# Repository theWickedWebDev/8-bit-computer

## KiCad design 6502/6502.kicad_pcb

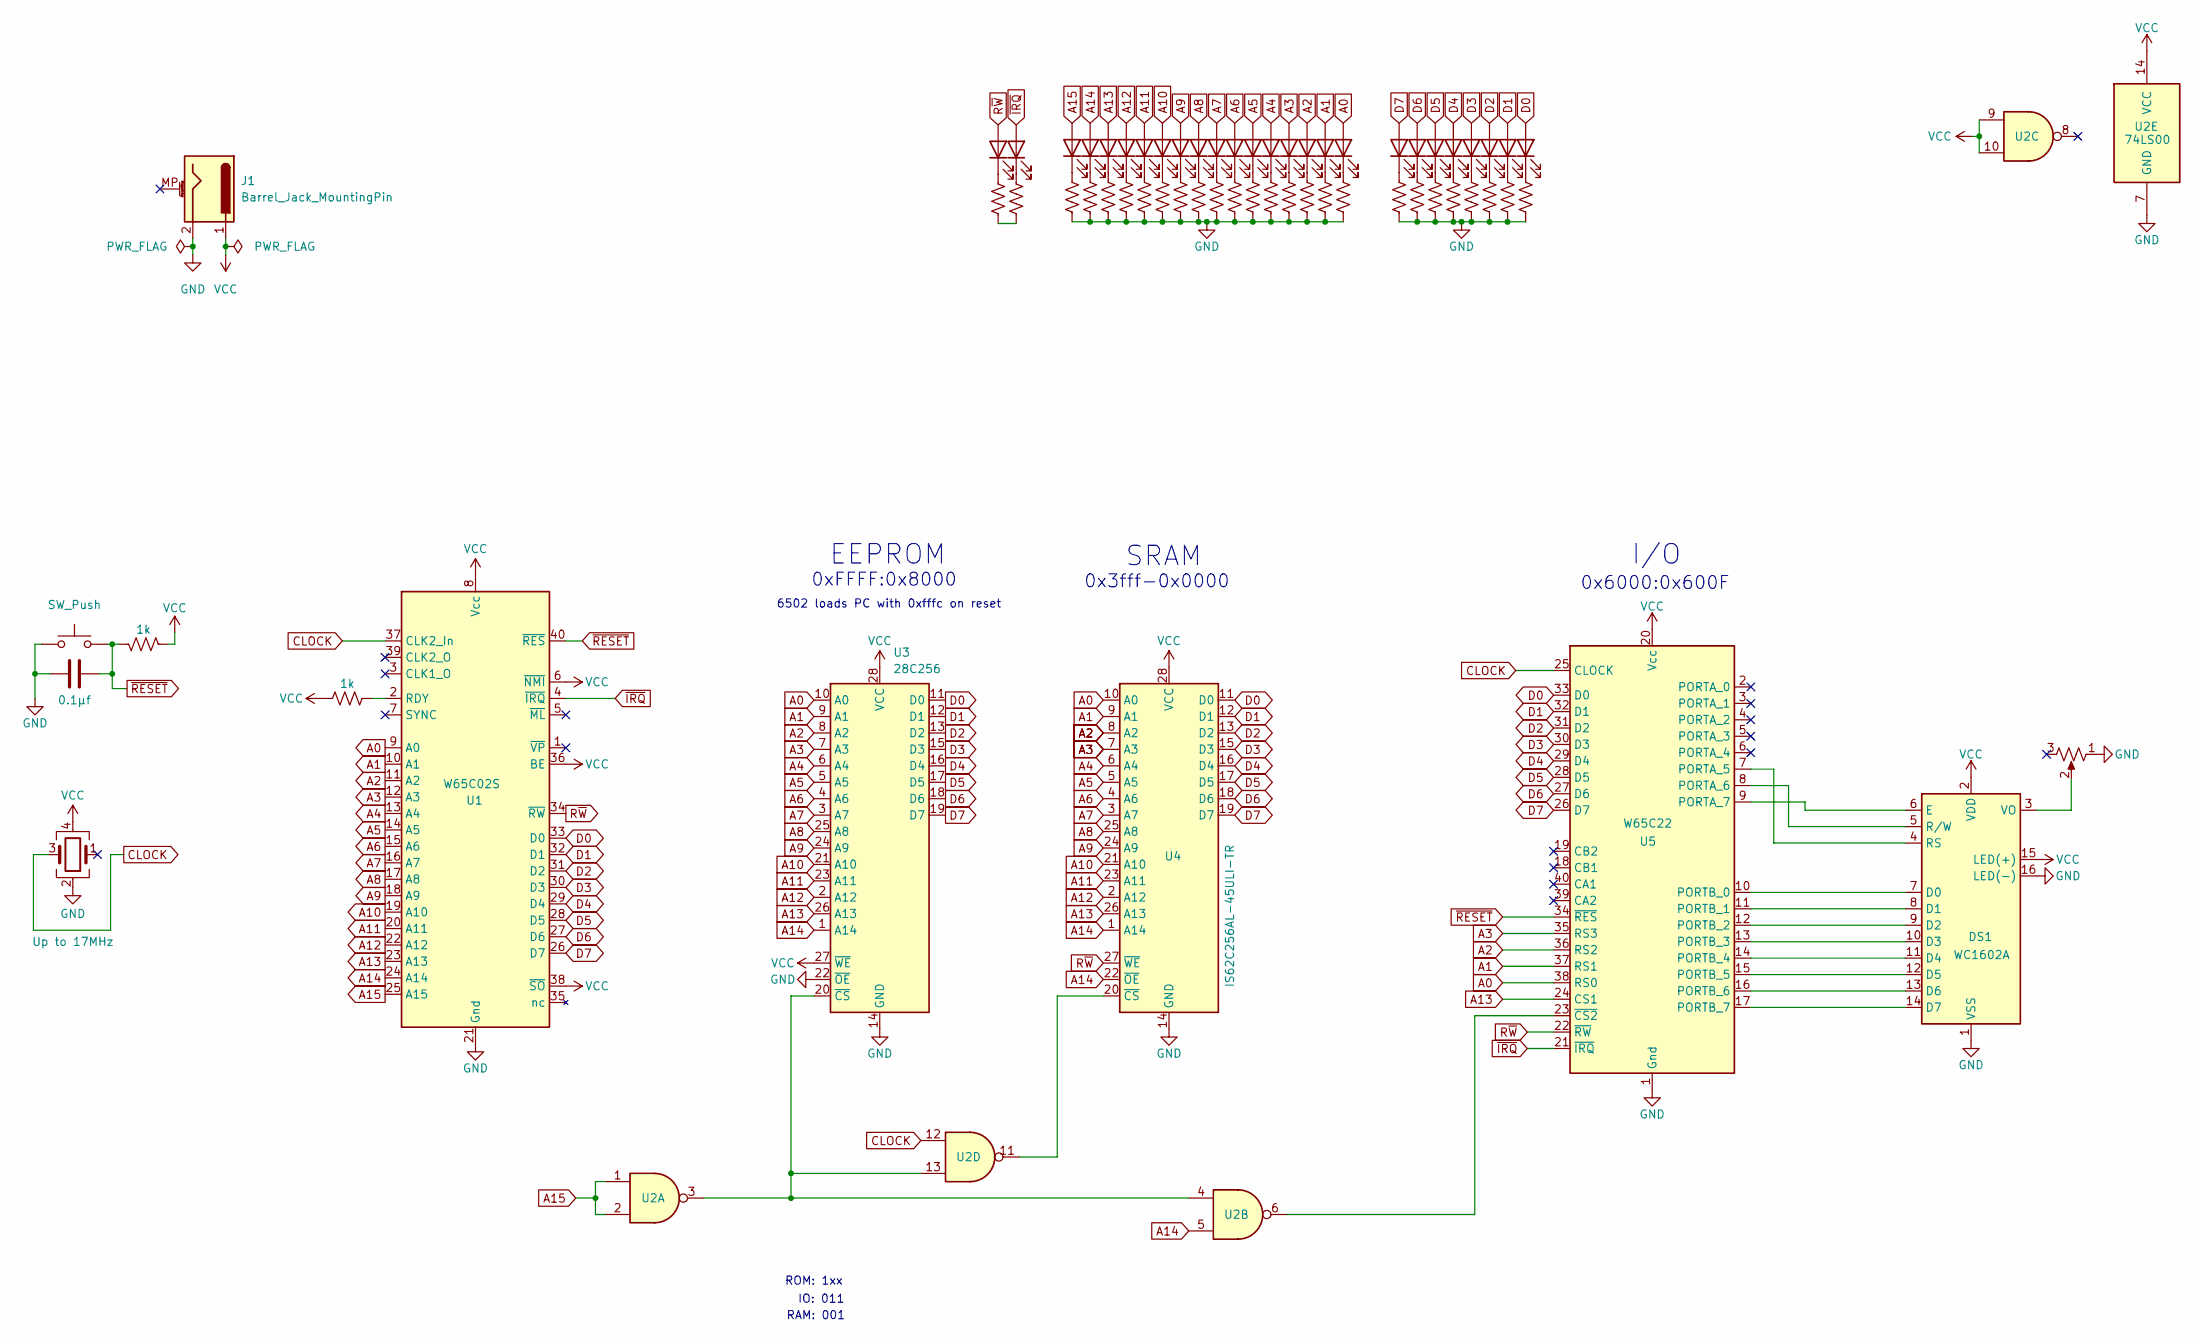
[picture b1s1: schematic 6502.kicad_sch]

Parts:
C1: C; C_0805_2012Metric
D1, D2, D3, D4, D5, D6, D7, D8, D9, D10, D11, D12, D13, D14, D15, D16, D17, D18, D19, D20, D21, D22, D23, D24, D25, D26: LED; LED_0805_2012Metric
DS1: WC1602A
J1: Barrel_Jack_MountingPin; BarrelJack_Horizontal
R1, R2, R3, R4, R5, R6, R7, R8, R9, R10, R11, R12, R13, R14, R15, R16, R17, R18, R19, R20, R21, R22, R23, R24, R25, R26, R27, R28: R_US; R_0805_2012Metric
RV1: R_Potentiometer_US; Potentiometer_Bourns_3224J_Horizontal
SW1: SW_Push; SW_PUSH_6mm
U1: W65C02S; PQFP-44_10x10mm_P0.8mm
U2: 74LS00; TSSOP-14_4.4x5mm_P0.65mm
U3: 28C256; Microchip-32J-10_2001-B-IPC_A
U4: IS62C256AL-45ULI-TR; SOIC-28W_7.5x17.9mm_P1.27mm
U5: W65C22; PQFP-44_10x10mm_P0.8mm
Y1: Crystal_GND24; Crystal_SMD_Abracon_ABM3C-4Pin_5.0x3.2mm

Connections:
A0: D18.2 (A), U1.9 (A0), U3.10 (A0), U4.10 (A0), U5.38 (RS0)
A1: D17.2 (A), U1.10 (A1), U3.9 (A1), U4.9 (A1), U5.37 (RS1)
A2: D16.2 (A), U1.11 (A2), U3.8 (A2), U4.8 (A2), U5.36 (RS2)
A3: D15.2 (A), U1.12 (A3), U3.7 (A3), U4.7 (A3), U5.35 (RS3)
A4: D14.2 (A), U1.13 (A4), U3.6 (A4), U4.6 (A4)
A5: D13.2 (A), U1.14 (A5), U3.5 (A5), U4.5 (A5)
A6: D12.2 (A), U1.15 (A6), U3.4 (A6), U4.4 (A6)
A7: D11.2 (A), U1.16 (A7), U3.3 (A7), U4.3 (A7)
A8: D10.2 (A), U1.17 (A8), U3.25 (A8), U4.25 (A8)
A9: D9.2 (A), U1.18 (A9), U3.24 (A9), U4.24 (A9)
A10: D8.2 (A), U1.19 (A10), U3.21 (A10), U4.21 (A10)
A11: D7.2 (A), U1.20 (A11), U3.23 (A11), U4.23 (A11)
A12: D6.2 (A), U1.22 (A12), U3.2 (A12), U4.2 (A12)
A13: D5.2 (A), U1.23 (A13), U3.26 (A13), U4.26 (A13), U5.24 (CS1)
A14: D4.2 (A), U1.24 (A14), U2.5, U3.1 (A14), U4.1 (A14), U4.22 (~OE)
A15: D3.2 (A), U1.25 (A15), U2.1, U2.2
CLOCK: U1.37 (CLK2_In), U2.12, U5.25 (CLOCK), Y1.3
D0: D26.2 (A), U1.33 (D0), U3.11 (D0), U4.11 (D0), U5.33 (D0)
D1: D25.2 (A), U1.32 (D1), U3.12 (D1), U4.12 (D1), U5.32 (D1)
D2: D24.2 (A), U1.31 (D2), U3.13 (D2), U4.13 (D2), U5.31 (D2)
D3: D23.2 (A), U1.30 (D3), U3.15 (D3), U4.15 (D3), U5.30 (D3)
D4: D22.2 (A), U1.29 (D4), U3.16 (D4), U4.16 (D4), U5.29 (D4)
D5: D21.2 (A), U1.28 (D5), U3.17 (D5), U4.17 (D5), U5.28 (D5)
D6: D20.2 (A), U1.27 (D6), U3.18 (D6), U4.18 (D6), U5.27 (D6)
D7: D19.2 (A), U1.26 (D7), U3.19 (D7), U4.19 (D7), U5.26 (D7)
GND: C1.2, DS1.1 (VSS), DS1.16 (LED(-)), J1.2, R5.1, R6.1, R7.1, R8.1, R9.1, R10.1, R11.1, R12.1, R13.1, R14.1, R15.1, R16.1, R17.1, R18.1, R19.1, R20.1, R21.1, R22.1, R23.1, R24.1, R25.1, R26.1, R27.1, R28.1, RV1.1, SW1.2, U1.21 (Gnd), U2.7 (GND), U3.14 (GND), U3.22 (~OE), U4.14 (GND), U5.1 (Gnd), Y1.2
unnamed: D1.1 (K), R3.2
unnamed: D2.1 (K), R4.2
unnamed: D3.1 (K), R5.2
unnamed: D4.1 (K), R6.2
unnamed: D5.1 (K), R7.2
unnamed: D6.1 (K), R8.2
unnamed: D7.1 (K), R9.2
unnamed: D8.1 (K), R10.2
unnamed: D9.1 (K), R11.2
unnamed: D10.1 (K), R12.2
unnamed: D11.1 (K), R13.2
unnamed: D12.1 (K), R14.2
unnamed: D13.1 (K), R15.2
unnamed: D14.1 (K), R16.2
unnamed: D15.1 (K), R17.2
unnamed: D16.1 (K), R18.2
unnamed: D17.1 (K), R19.2
unnamed: D18.1 (K), R20.2
unnamed: D19.1 (K), R21.2
unnamed: D20.1 (K), R22.2
unnamed: D21.1 (K), R23.2
unnamed: D22.1 (K), R24.2
unnamed: D23.1 (K), R25.2
unnamed: D24.1 (K), R26.2
unnamed: D25.1 (K), R27.2
unnamed: D26.1 (K), R28.2
unnamed: DS1.3 (VO), RV1.2
unnamed: R2.2, U1.2 (RDY)
unnamed: R3.1, R4.1
unnamed: U2.11, U4.20 (~CS)
unnamed: U2.3, U2.4, U2.13, U3.20 (~CS)
unnamed: DS1.4 (RS), U5.7 (PORTA_5)
unnamed: DS1.5 (R/W), U5.8 (PORTA_6)
unnamed: DS1.6 (E), U5.9 (PORTA_7)
unnamed: DS1.7 (D0), U5.10 (PORTB_0)
unnamed: DS1.8 (D1), U5.11 (PORTB_1)
unnamed: DS1.9 (D2), U5.12 (PORTB_2)
unnamed: DS1.10 (D3), U5.13 (PORTB_3)
unnamed: DS1.11 (D4), U5.14 (PORTB_4)
unnamed: DS1.12 (D5), U5.15 (PORTB_5)
unnamed: DS1.13 (D6), U5.16 (PORTB_6)
unnamed: DS1.14 (D7), U5.17 (PORTB_7)
unnamed: U2.6, U5.23 (~CS2)
R~W: D1.2 (A), U1.34 (~RW), U4.27 (~WE), U5.22 (~RW)
VCC: DS1.2 (VDD), DS1.15 (LED(+)), J1.1, R1.1, R2.1, U1.6 (~NMI), U1.8 (Vcc), U1.36 (BE), U1.38 (~SO), U2.9, U2.10, U2.14 (VCC), U3.27 (~WE), U3.28 (VCC), U4.28 (VCC), U5.20 (Vcc), Y1.4
~IRQ: D2.2 (A), U1.4 (~IRQ), U5.21 (~IRQ)
~RESET: C1.1, R1.2, SW1.1, U1.40 (~RES), U5.34 (~RES)

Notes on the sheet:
0xFFFF:0x8000
I/O
ROM: 1xx
0x3fff-0x0000
IO: 011
0x6000:0x600F
RAM: 001
EEPROM
6502 loads PC with 0xfffc on reset
SRAM

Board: 2 copper layers, 65 parts (0 on the bottom side), 73 nets, no tracks yet.

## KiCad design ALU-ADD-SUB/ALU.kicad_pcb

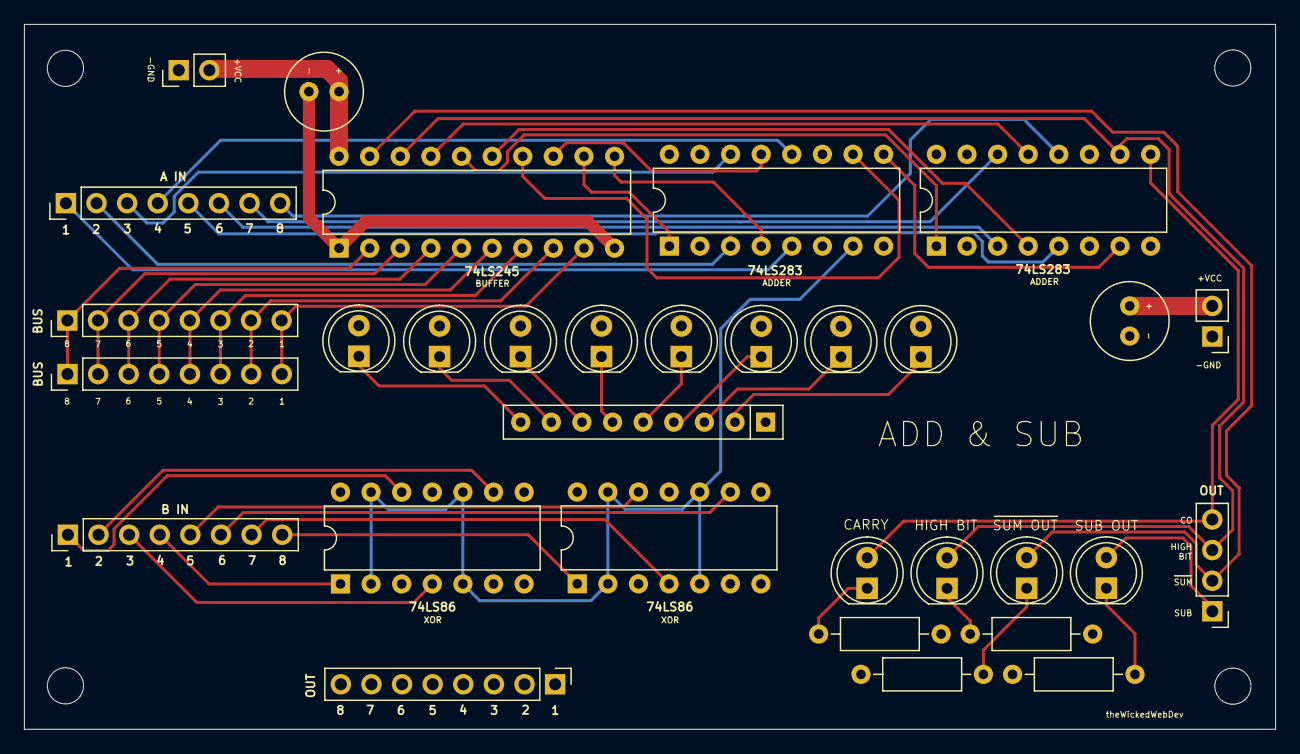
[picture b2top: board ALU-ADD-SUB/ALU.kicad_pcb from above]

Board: 4 copper layers, 103.8 x 58.5 mm, 32 parts (0 on the bottom side), 58 nets.

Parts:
C4, C5: CP1; C_Radial_D6.3mm_H11.0mm_P2.50mm
D1, D2, D3, D4, D5, D6, D7, D8, D25, D26, D27, D28: LED; LED_D5.0mm
J1, J7: Conn_01x02; PinHeader_1x02_P2.54mm_Vertical
J2, J3, J4, J6, J8: Conn_01x08; PinHeader_1x08_P2.54mm_Vertical
J5: Conn_01x04; PinHeader_1x04_P2.54mm_Vertical
R1, R2, R3, R4: R_Small_US; R_Axial_DIN0207_L6.3mm_D2.5mm_P10.16mm_Horizontal
RN1: R_Network08_US; R_Array_SIP9
U11: 74LS245; DIP-20_W7.62mm
U12, U13: 74LS283; DIP-16_W7.62mm
U14, U15: 74LS86; DIP-14_W7.62mm

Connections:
/CARRY_OUT: D28.2, J5.4, U12.9
/SUB: D25.2, J5.1, U13.7, U14.2, U14.5, U14.10, U14.13, U15.2, U15.5, U15.10, U15.13
/SUM1: D8.2, J8.1, U11.11, U13.4
/SUM2: D7.2, J8.2, U11.12, U13.1
/SUM3: D6.2, J8.3, U11.13, U13.13
/SUM4: D5.2, J8.4, U11.14, U13.10
/SUM5: D4.2, J8.5, U11.15, U12.4
/SUM6: D3.2, J8.6, U11.16, U12.1
/SUM7: D2.2, J8.7, U11.17, U12.13
/SUM8: D1.2, D27.2, J5.3, J8.8, U11.18, U12.10
/SUM_OUT: D26.2, J5.2, U11.19
/Y1: J4.8, J6.8, U11.9
/Y2: J4.7, J6.7, U11.8
/Y3: J4.6, J6.6, U11.7
/Y4: J4.5, J6.5, U11.6
/Y5: J4.4, J6.4, U11.5
/Y6: J4.3, J6.3, U11.4
/Y7: J4.2, J6.2, U11.3
/Y8: J4.1, J6.1, U11.2
A1: J2.1, U13.5
A2: J2.2, U13.3
A3: J2.3, U13.14
A4: J2.4, U13.12
A5: J2.5, U12.5
A6: J2.6, U12.3
A7: J2.7, U12.14
A8: J2.8, U12.12
B1: J3.1, U15.12
B2: J3.2, U15.9
B3: J3.3, U15.4
B4: J3.4, U15.1
B5: J3.5, U14.12
B6: J3.6, U14.9
B7: J3.7, U14.4
B8: J3.8, U14.1
GND: C4.2, C5.2, J1.1, J7.1, R1.2, R2.2, R3.2, R4.2, RN1.1, U11.1, U11.10, U12.8, U13.8, U14.7, U15.7
unnamed: D1.1, RN1.9
unnamed: D2.1, RN1.8
unnamed: D3.1, RN1.7
unnamed: D4.1, RN1.6
unnamed: D5.1, RN1.5
unnamed: D6.1, RN1.4
unnamed: D7.1, RN1.3
unnamed: D8.1, RN1.2
unnamed: D25.1, R1.1
unnamed: D26.1, R2.1
unnamed: D27.1, R3.1
unnamed: D28.1, R4.1
unnamed: U12.2, U14.8
unnamed: U12.6, U14.11
unnamed: U12.7, U13.9
unnamed: U12.11, U14.3
unnamed: U12.15, U14.6
unnamed: U13.2, U15.8
unnamed: U13.6, U15.11
unnamed: U13.11, U15.3
unnamed: U13.15, U15.6
VCC: C4.1, C5.1, J1.2, J7.2, U11.20, U12.16, U13.16, U14.14, U15.14

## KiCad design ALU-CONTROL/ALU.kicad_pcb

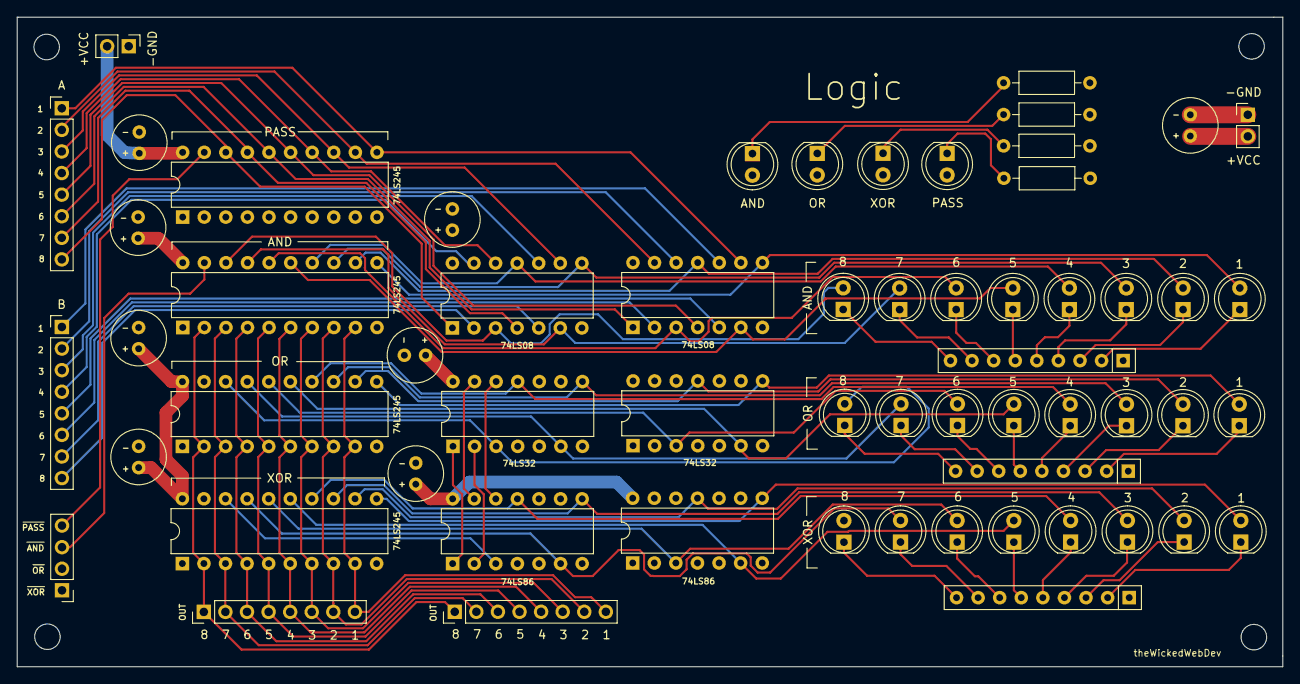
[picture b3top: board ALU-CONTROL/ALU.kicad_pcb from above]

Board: 4 copper layers, 148.9 x 76.4 mm, 60 parts (0 on the bottom side), 82 nets.

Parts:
C1, C2, C3, C4, C5, C6, C7, C8: CP1; C_Radial_D6.3mm_H11.0mm_P2.50mm
D1, D2, D3, D4, D5, D6, D7, D8, D9, D10, D11, D12, D13, D14, D15, D16, D17, D18, D19, D20, D21, D22, D23, D24, D25, D26, D27, D28: LED; LED_D5.0mm
J1, J7: Conn_01x02; PinHeader_1x02_P2.54mm_Vertical
J2, J3, J4, J6: Conn_01x08; PinHeader_1x08_P2.54mm_Vertical
J5: Conn_01x04; PinHeader_1x04_P2.54mm_Vertical
R1, R2, R3, R4: R_Small_US; R_Axial_DIN0207_L6.3mm_D2.5mm_P10.16mm_Horizontal
RN1, RN2, RN3: R_Network08_US; R_Array_SIP9
U1, U3: 74LS08; DIP-14_W7.62mm
U2, U6, U8, U10: 74LS245; DIP-20_W7.62mm
U4, U7: 74LS32; DIP-14_W7.62mm
U5, U9: 74LS86; DIP-14_W7.62mm

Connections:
/AND_OUT: D27.2, J5.3, U2.19
/OR_OUT: D26.2, J5.2, U6.19
/PASS: D28.2, J5.4, U10.19
/XOR_OUT: D25.2, J5.1, U8.19
/Y1: J4.8, J6.8, U2.9, U6.9, U8.9, U10.9
/Y2: J4.7, J6.7, U2.8, U6.8, U8.8, U10.8
/Y3: J4.6, J6.6, U2.7, U6.7, U8.7, U10.7
/Y4: J4.5, J6.5, U2.6, U6.6, U8.6, U10.6
/Y5: J4.4, J6.4, U2.5, U6.5, U8.5, U10.5
/Y6: J4.3, J6.3, U2.4, U6.4, U8.4, U10.4
/Y7: J4.2, J6.2, U2.3, U6.3, U8.3, U10.3
/Y8: J4.1, J6.1, U2.2, U6.2, U8.2, U10.2
A1: J2.1, U3.9, U7.9, U9.9, U10.11
A2: J2.2, U3.13, U7.13, U9.13, U10.12
A3: J2.3, U1.9, U4.9, U5.9, U10.13
A4: J2.4, U1.12, U4.12, U5.12, U10.14
A5: J2.5, U3.4, U7.4, U9.4, U10.15
A6: J2.6, U3.1, U7.1, U9.1, U10.16
A7: J2.7, U1.4, U4.4, U5.4, U10.17
A8: J2.8, U1.1, U4.1, U5.1, U10.18
B1: J3.1, U3.10, U7.10, U9.10
B2: J3.2, U3.12, U7.12, U9.12
B3: J3.3, U1.10, U4.10, U5.10
B4: J3.4, U1.13, U4.13, U5.13
B5: J3.5, U3.5, U7.5, U9.5
B6: J3.6, U3.2, U7.2, U9.2
B7: J3.7, U1.5, U4.5, U5.5
B8: J3.8, U1.2, U4.2, U5.2
GND: C1.2, C2.2, C3.2, C4.2, C5.2, C6.2, C7.2, C8.2, J1.1, J7.1, R1.2, R2.2, R3.2, R4.2, RN1.1, RN2.1, RN3.1, U1.7, U2.1, U2.10, U3.7, U4.7, U5.7, U6.1, U6.10, U7.7, U8.1, U8.10, U9.7, U10.1, U10.10
unnamed: D1.1, RN1.9
unnamed: D1.2, U1.3, U2.18
unnamed: D2.1, RN1.8
unnamed: D2.2, U1.6, U2.17
unnamed: D3.1, RN1.7
unnamed: D3.2, U2.16, U3.3
unnamed: D4.1, RN1.6
unnamed: D4.2, U2.15, U3.6
unnamed: D5.1, RN1.5
unnamed: D5.2, U1.11, U2.14
unnamed: D6.1, RN1.4
unnamed: D6.2, U1.8, U2.13
unnamed: D7.1, RN1.3
unnamed: D7.2, U2.12, U3.11
unnamed: D8.1, RN1.2
unnamed: D8.2, U2.11, U3.8
unnamed: D9.1, RN2.9
unnamed: D10.1, RN2.8
unnamed: D10.2, U4.6, U6.17
unnamed: D11.1, RN2.7
unnamed: D11.2, U6.16, U7.3
unnamed: D12.1, RN2.6
unnamed: D12.2, U6.15, U7.6
unnamed: D13.1, RN2.5
unnamed: D13.2, U4.11, U6.14
unnamed: D14.1, RN2.4
unnamed: D14.2, U4.8, U6.13
unnamed: D15.1, RN2.3
unnamed: D15.2, U6.12, U7.11
unnamed: D16.1, RN2.2
unnamed: D16.2, U6.11, U7.8
unnamed: D17.1, RN3.9
unnamed: D17.2, U5.3, U8.18
unnamed: D18.1, RN3.8
unnamed: D18.2, U5.6, U8.17
unnamed: D19.1, RN3.7
unnamed: D19.2, U8.16, U9.3
unnamed: D20.1, RN3.6
unnamed: D20.2, U8.15, U9.6
unnamed: D21.1, RN3.5
unnamed: D21.2, U5.11, U8.14
unnamed: D22.1, RN3.4
unnamed: D22.2, U5.8, U8.13
unnamed: D23.1, RN3.3
unnamed: D23.2, U8.12, U9.11
unnamed: D24.1, RN3.2
unnamed: D24.2, U8.11, U9.8
unnamed: D25.1, R1.1
unnamed: D26.1, R2.1
unnamed: D27.1, R3.1
unnamed: D28.1, R4.1
unnamed: D9.2, U4.3, U6.18
VCC: C1.1, C2.1, C3.1, C4.1, C5.1, C6.1, C7.1, C8.1, J1.2, J7.2, U1.14, U2.20, U3.14, U4.14, U5.14, U6.20, U7.14, U8.20, U9.14, U10.20

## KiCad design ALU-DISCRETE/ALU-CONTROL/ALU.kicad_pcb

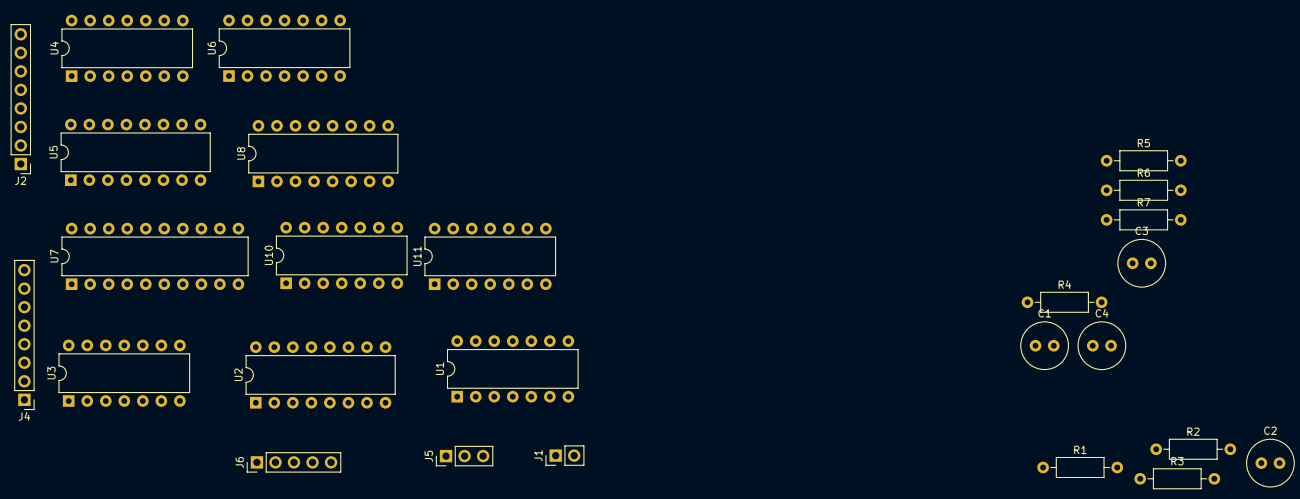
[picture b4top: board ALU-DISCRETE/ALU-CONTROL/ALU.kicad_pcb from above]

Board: 4 copper layers, 26 parts (0 on the bottom side), 58 nets, no tracks yet.

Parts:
C1, C2, C3, C4: CP1; C_Radial_D6.3mm_H11.0mm_P2.50mm
J1: Conn_01x02; PinHeader_1x02_P2.54mm_Vertical
J2, J4: Conn_01x08; PinHeader_1x08_P2.54mm_Vertical
J5: Conn_01x03; PinHeader_1x03_P2.54mm_Vertical
J6: Conn_01x05; PinHeader_1x05_P2.54mm_Vertical
R1, R2, R3, R4, R5, R6, R7: R_US; R_Axial_DIN0207_L6.3mm_D2.5mm_P10.16mm_Horizontal
U1, U3, U11: 74LS08; DIP-14_W7.62mm
U2: 74LS138; DIP-16_W7.62mm
U4, U6: 74LS04; DIP-14_W7.62mm
U5, U8: 74LS157; DIP-16_W7.62mm
U7: 74LS245; DIP-20_W7.62mm
U10: 74LS02; DIP-14_W7.62mm

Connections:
/ALU_EN: J6.5, U7.19
/ALU_OUT1: J4.1, U7.9
/ALU_OUT2: J4.2, U7.8
/ALU_OUT3: J4.3, U7.7
/ALU_OUT4: J4.4, U7.6
/ALU_OUT5: J4.5, U7.5
/ALU_OUT6: J4.6, U7.4
/ALU_OUT7: J4.7, U7.3
/ALU_OUT8: J4.8, U7.2
/EQ: U1.5, U3.8
/F0: J6.1, U2.1
/F1: J6.2, U2.2
/F2: J6.3, U2.3
/INVERT: J6.4, U5.1, U8.1
/NEG: J5.2, U1.3
/SUB: U1.1, U1.4, U4.6
/Y1: J2.8, U6.3, U8.3
/Y2: J2.7, U6.1, U8.6
/Y3: J2.6, U4.13, U8.10
/Y4: J2.5, U4.11, U8.13
/Y5: J2.4, U4.9, U5.2
/Y6: J2.3, U5.5, U6.5
/Y7: J2.2, U4.3, U5.11
/Y8: J2.1, U4.1, U5.14
/ZE: J5.3, U1.6
GND: C1.2, C2.2, C3.2, C4.2, J1.1, R1.1, R2.1, R3.1, R4.1, R5.1, R6.1, R7.1, U1.7, U2.4, U2.5, U2.8, U3.7, U4.7, U5.8, U5.15, U6.7, U7.1, U7.10, U8.8, U8.15, U10.7, U11.7
unnamed: R1.2, U1.10
unnamed: R2.2, U1.9
unnamed: R3.2, U6.9
unnamed: R4.2, U6.11
unnamed: R5.2, U6.13
unnamed: R6.2, U3.13
unnamed: R7.2, U3.12
unnamed: U2.14, U3.1, U4.5
unnamed: U2.15, U3.2
unnamed: U4.2, U5.13
unnamed: U4.4, U5.10
unnamed: U4.8, U5.3
unnamed: U4.10, U8.14
unnamed: U4.12, U8.11
unnamed: U5.4, U7.15
unnamed: U5.6, U6.6
unnamed: U5.7, U7.16
unnamed: U5.9, U7.17
unnamed: U5.12, U7.18
unnamed: U6.2, U8.5
unnamed: U6.4, U8.2
unnamed: U7.11, U8.4
unnamed: U7.12, U8.7
unnamed: U7.13, U8.9
unnamed: U7.14, U8.12
unnamed: U10.1, U11.2
unnamed: U10.4, U11.1
unnamed: U10.10, U11.5
unnamed: U10.13, U11.4
unnamed: U3.10, U11.3
unnamed: U3.9, U11.6
VCC: C1.1, C2.1, C3.1, C4.1, J1.2, U1.14, U2.6, U2.16, U3.14, U4.14, U5.16, U6.14, U7.20, U8.16, U10.14, U11.14

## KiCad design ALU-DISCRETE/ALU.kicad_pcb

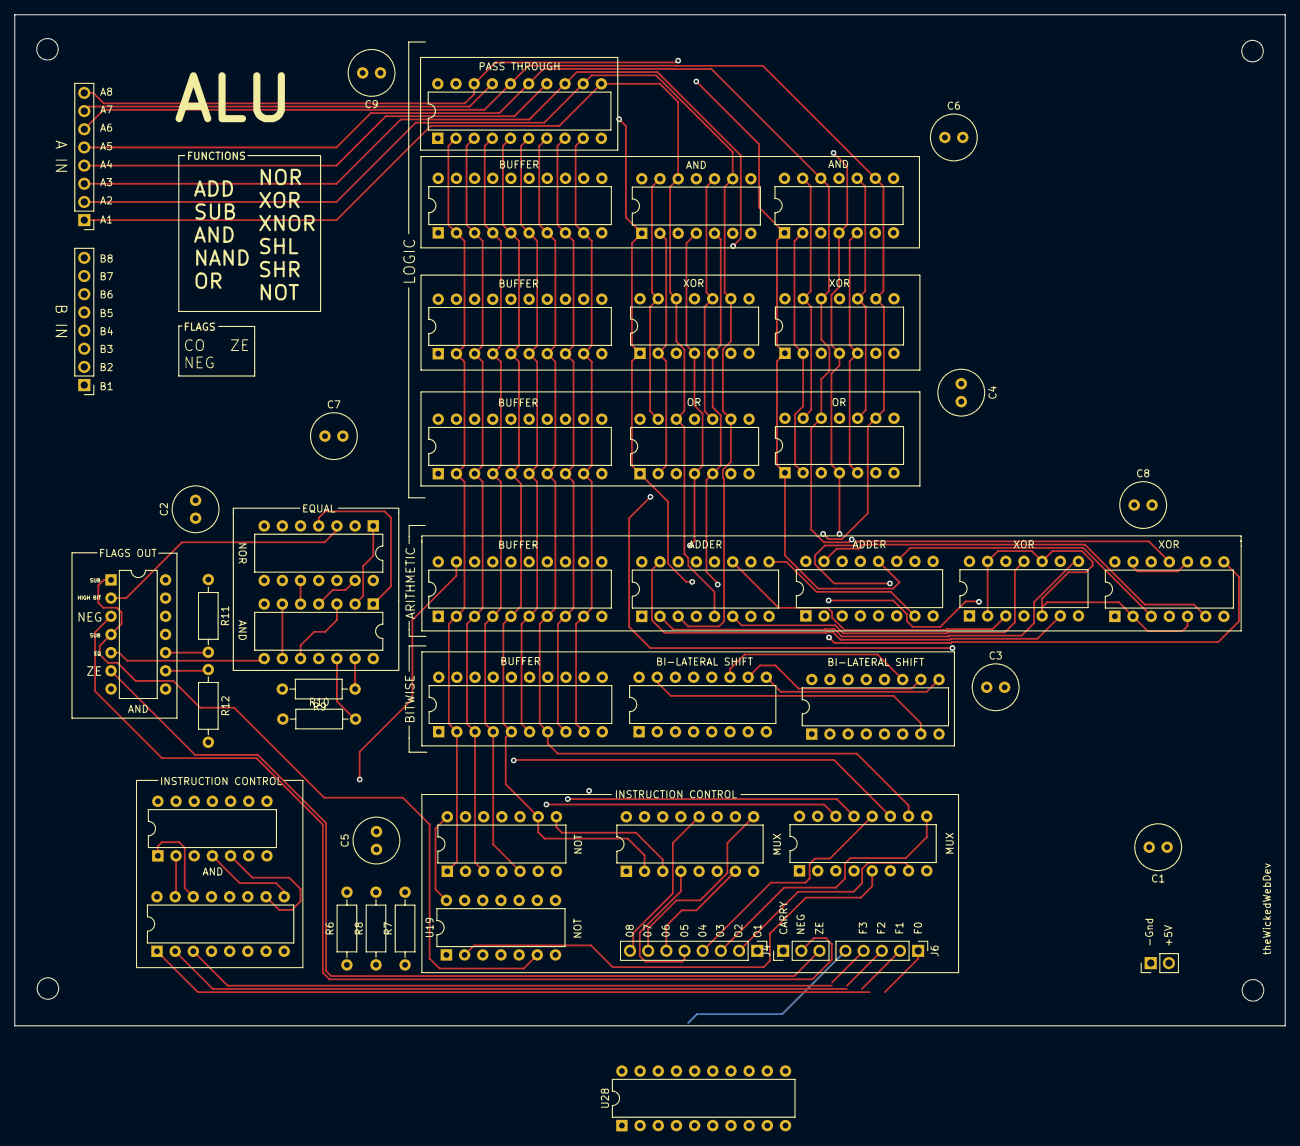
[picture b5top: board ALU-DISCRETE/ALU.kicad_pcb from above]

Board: 4 copper layers, 177.5 x 141.3 mm, 50 parts (0 on the bottom side), 133 nets.

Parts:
C1, C2, C3, C4, C5, C6, C7, C8, C9: CP1; C_Radial_D6.3mm_H11.0mm_P2.50mm
J1, J2, J3: Conn_01x08; PinHeader_1x08_P2.54mm_Vertical
J4: Conn_01x03; PinHeader_1x03_P2.54mm_Vertical
J5: Conn_01x02; PinHeader_1x02_P2.54mm_Vertical
J6: Conn_01x05; PinHeader_1x05_P2.54mm_Vertical
R6, R7, R8, R9, R10, R11, R12: R_US; R_Axial_DIN0207_L6.3mm_D2.5mm_P10.16mm_Horizontal
U1, U7, U11, U25, U27: 74LS08; DIP-14_W7.62mm
U2, U10, U21, U23: 74LS86; DIP-14_W7.62mm
U3, U9: 74LS32; DIP-14_W7.62mm
U4: 74LS02; DIP-14_W7.62mm
U5, U6, U8, U13, U14, U24, U28: 74LS245; DIP-20_W7.62mm
U12, U19: 74LS04; DIP-14_W7.62mm
U15, U17: 74LS283; DIP-16_W7.62mm
U16, U20: 74LS157; DIP-16_W7.62mm
U18, U22: 74LS194; DIP-16_W7.62mm
U26: 74LS138; DIP-16_W7.62mm

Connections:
/ALU_EN: J6.5, U28.19
/ALU_OUT1: J3.1, U28.9
/ALU_OUT2: J3.2, U28.8
/ALU_OUT3: J3.3, U28.7
/ALU_OUT4: J3.4, U28.6
/ALU_OUT5: J3.5, U28.5
/ALU_OUT6: J3.6, U28.4
/ALU_OUT7: J3.7, U28.3
/ALU_OUT8: J3.8, U28.2
/AND_OUT: U5.19, U26.13
/CARRY_OUT: J4.1, U15.9
/CLOCK: U18.11, U22.11
/EQ: U11.8, U25.5
/F0: J6.1, U26.1
/F1: J6.2, U26.2
/F2: J6.3, U26.3
/INVERT: J6.4, U16.1, U20.1
/NEG: J4.2, U25.3
/OR_OUT: U6.19, U26.12
/PASS: U13.19, U26.7
/SHIFT_EN: U24.19, U27.6
/SHL: U18.10, U22.10, U26.10, U27.5
/SHR: U18.9, U22.9, U26.9, U27.4
/SUB: U17.7, U19.6, U21.2, U21.5, U21.10, U21.13, U23.2, U23.5, U23.10, U23.13, U25.1, U25.4
/SUM1: U4.11, U14.11, U17.4
/SUM2: U4.12, U14.12, U17.1
/SUM3: U4.8, U14.13, U17.13
/SUM4: U4.9, U14.14, U17.10
/SUM5: U4.5, U14.15, U15.4
/SUM6: U4.6, U14.16, U15.1
/SUM7: U4.2, U14.17, U15.13
/SUM8: U4.3, U14.18, U15.10, U25.2
/SUM_OUT: U14.19, U27.3
/XOR_OUT: U8.19, U26.11
/Y1: U5.9, U6.9, U8.9, U13.9, U14.9, U19.3, U20.3, U24.9
/Y2: U5.8, U6.8, U8.8, U13.8, U14.8, U19.1, U20.6, U24.8
/Y3: U5.7, U6.7, U8.7, U12.13, U13.7, U14.7, U20.10, U24.7
/Y4: U5.6, U6.6, U8.6, U12.11, U13.6, U14.6, U20.13, U24.6
/Y5: U5.5, U6.5, U8.5, U12.9, U13.5, U14.5, U16.2, U24.5
/Y6: U5.4, U6.4, U8.4, U12.5, U13.4, U14.4, U16.5, U24.4
/Y7: U5.3, U6.3, U8.3, U12.3, U13.3, U14.3, U16.11, U24.3
/Y8: U5.2, U6.2, U8.2, U12.1, U13.2, U14.2, U16.14, U24.2
/ZE: J4.3, U25.6
A1: J1.1, U7.12, U9.12, U10.12, U13.11, U17.5, U22.6
A2: J1.2, U7.9, U9.9, U10.9, U13.12, U17.3, U22.5
A3: J1.3, U7.4, U9.4, U10.4, U13.13, U17.14, U22.4
A4: J1.4, U7.1, U9.1, U10.1, U13.14, U17.12, U22.3
A5: J1.5, U1.12, U2.12, U3.12, U13.15, U15.5, U18.6
A6: J1.6, U1.9, U2.9, U3.9, U13.16, U15.3, U18.5
A7: J1.7, U1.4, U2.4, U3.4, U13.17, U15.14, U18.4
A8: J1.8, U1.1, U2.1, U3.1, U13.18, U15.12, U18.3
B1: J2.1, U7.13, U9.13, U10.13, U23.12
B2: J2.2, U7.10, U9.10, U10.10, U23.9
B3: J2.3, U7.5, U9.5, U10.5, U23.4
B4: J2.4, U7.2, U9.2, U10.2, U23.1
B5: J2.5, U1.13, U2.13, U3.13, U21.12
B6: J2.6, U1.10, U2.10, U3.10, U21.9
B7: J2.7, U1.5, U2.5, U3.5, U21.4
B8: J2.8, U1.2, U2.2, U3.2, U21.1
GND: C1.2, C2.2, C3.2, C4.2, C5.2, C6.2, C7.2, C8.2, C9.2, J5.1, R6.1, R7.1, R8.1, R9.1, R10.1, R11.1, R12.1, U1.7, U2.7, U3.7, U4.7, U5.1, U5.10, U6.1, U6.10, U7.7, U8.1, U8.10, U9.7, U10.7, U11.7, U12.7, U13.1, U13.10, U14.1, U14.10, U15.8, U16.8, U16.15, U17.8, U18.2, U18.8, U19.7, U20.8, U20.15, U21.7, U22.7, U22.8, U23.7, U24.1, U24.10, U25.7, U26.4, U26.5, U26.8, U27.7, U28.1, U28.10
unnamed: R6.2, U19.9
unnamed: R7.2, U19.11
unnamed: R8.2, U19.13
unnamed: R9.2, U11.13
unnamed: R10.2, U11.12
unnamed: R11.2, U25.10
unnamed: R12.2, U25.9
unnamed: U1.3, U5.18
unnamed: U1.6, U5.17
unnamed: U1.8, U5.16
unnamed: U1.11, U5.15
unnamed: U2.3, U8.18
unnamed: U2.6, U8.17
unnamed: U2.8, U8.16
unnamed: U2.11, U8.15
unnamed: U3.3, U6.18
unnamed: U3.6, U6.17
unnamed: U3.8, U6.16
unnamed: U3.11, U6.15
unnamed: U5.11, U7.11
unnamed: U5.12, U7.8
unnamed: U5.13, U7.6
unnamed: U5.14, U7.3
unnamed: U6.11, U9.11
unnamed: U6.12, U9.8
unnamed: U6.13, U9.6
unnamed: U6.14, U9.3
unnamed: U8.14, U10.3
unnamed: U8.13, U10.6
unnamed: U8.12, U10.8
unnamed: U8.11, U10.11
unnamed: U4.4, U11.1
unnamed: U4.1, U11.2
unnamed: U4.13, U11.4
unnamed: U4.10, U11.5
unnamed: U11.6, U11.9
unnamed: U11.3, U11.10
unnamed: U12.2, U16.13
unnamed: U12.4, U16.10
unnamed: U12.6, U16.6
unnamed: U12.8, U16.3
unnamed: U12.10, U20.14
unnamed: U12.12, U20.11
unnamed: U15.2, U21.8
unnamed: U15.6, U21.11
unnamed: U15.7, U17.9
unnamed: U15.11, U21.3
unnamed: U15.15, U21.6
unnamed: U16.4, U28.15
unnamed: U16.7, U28.16
unnamed: U16.9, U28.17
unnamed: U16.12, U28.18
unnamed: U17.2, U23.8
unnamed: U17.6, U23.11
unnamed: U17.11, U23.3
unnamed: U17.15, U23.6
unnamed: U18.7, U22.15, U24.14
unnamed: U18.12, U22.2, U24.15
unnamed: U18.13, U24.16
unnamed: U18.14, U24.17
unnamed: U18.15, U24.18
unnamed: U19.2, U20.5
unnamed: U19.4, U20.2
unnamed: U19.5, U26.14, U27.1
unnamed: U20.4, U28.11
unnamed: U20.7, U28.12
unnamed: U20.9, U28.13
unnamed: U20.12, U28.14
unnamed: U22.12, U24.11
unnamed: U22.13, U24.12
unnamed: U22.14, U24.13
unnamed: U26.15, U27.2
VCC: C1.1, C2.1, C3.1, C4.1, C5.1, C6.1, C7.1, C8.1, C9.1, J5.2, U1.14, U2.14, U3.14, U4.14, U5.20, U6.20, U7.14, U8.20, U9.14, U10.14, U11.14, U12.14, U13.20, U14.20, U15.16, U16.16, U17.16, U18.1, U18.16, U19.14, U20.16, U21.14, U22.1, U22.16, U23.14, U24.20, U25.14, U26.6, U26.16, U27.14, U28.20

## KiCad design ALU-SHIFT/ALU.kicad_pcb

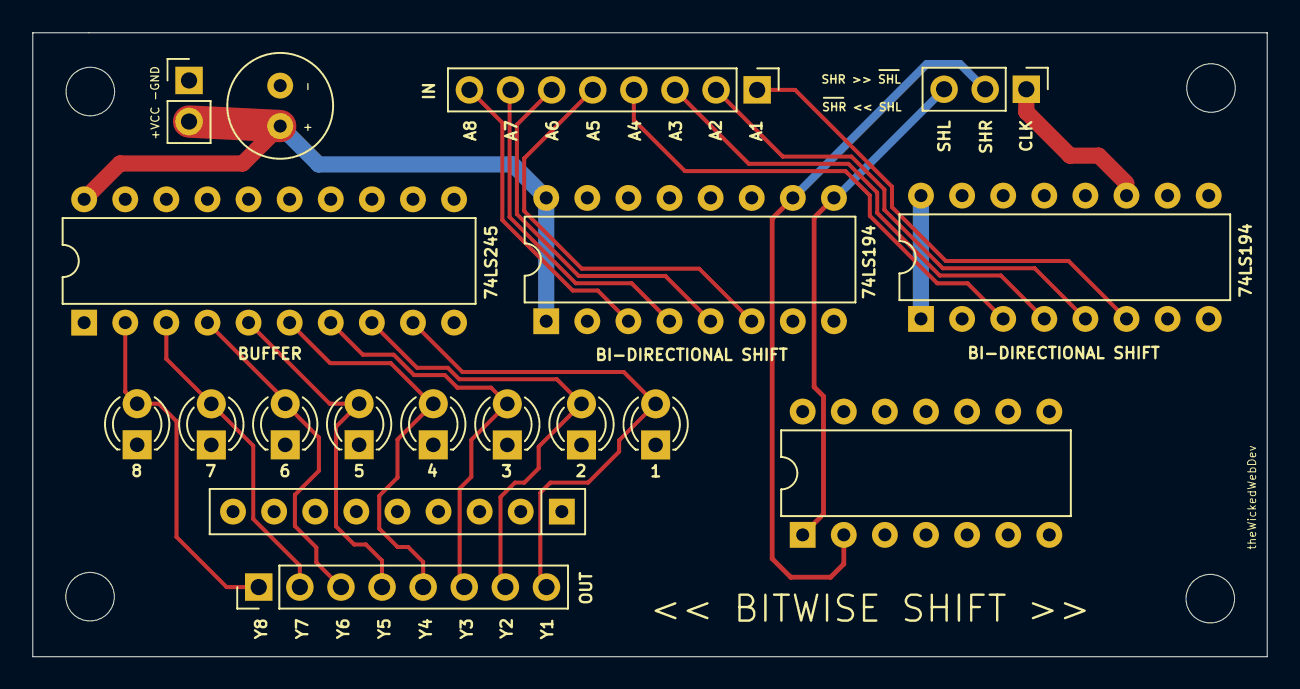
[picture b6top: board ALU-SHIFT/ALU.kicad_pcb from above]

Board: 4 copper layers, 76.3 x 38.6 mm, 18 parts (0 on the bottom side), 38 nets.

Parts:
C1: CP1; C_Radial_D6.3mm_H11.0mm_P2.50mm
D1, D2, D3, D4, D5, D6, D7, D8: LED; LED_D3.0mm
J1: Conn_01x02; PinHeader_1x02_P2.54mm_Vertical
J2, J3: Conn_01x08; PinHeader_1x08_P2.54mm_Vertical
J4: Conn_01x03; PinHeader_1x03_P2.54mm_Vertical
RN1: R_Network08_US; R_Array_SIP9
U1, U2: 74LS194; DIP-16_W7.62mm
U3: 74LS245; DIP-20_W7.62mm
U4: 74LS08; DIP-14_W7.62mm

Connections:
/CLOCK: J4.1, U1.11, U2.11
/SHIFT_EN: U3.19, U4.3
/SHL: J4.2, U1.10, U2.10, U4.2
/SHR: J4.3, U1.9, U2.9, U4.1
/Y1: D8.2, J3.8, U3.9
/Y2: D7.2, J3.7, U3.8
/Y3: D6.2, J3.6, U3.7
/Y4: D5.2, J3.5, U3.6
/Y5: D4.2, J3.4, U3.5
/Y6: D3.2, J3.3, U3.4
/Y7: D2.2, J3.2, U3.3
/Y8: D1.2, J3.1, U3.2
A1: J2.1, U2.6
A2: J2.2, U2.5
A3: J2.3, U2.4
A4: J2.4, U2.3
A5: J2.5, U1.6
A6: J2.6, U1.5
A7: J2.7, U1.4
A8: J2.8, U1.3
GND: C1.2, J1.1, RN1.1, U1.2, U1.8, U2.7, U2.8, U3.1, U3.10, U4.7
unnamed: D1.1, RN1.9
unnamed: D2.1, RN1.8
unnamed: D3.1, RN1.7
unnamed: D4.1, RN1.6
unnamed: D5.1, RN1.5
unnamed: D6.1, RN1.4
unnamed: D7.1, RN1.3
unnamed: D8.1, RN1.2
unnamed: U1.7, U2.15, U3.14
unnamed: U1.12, U2.2, U3.15
unnamed: U1.13, U3.16
unnamed: U1.14, U3.17
unnamed: U1.15, U3.18
unnamed: U2.12, U3.11
unnamed: U2.13, U3.12
unnamed: U2.14, U3.13
VCC: C1.1, J1.2, U1.1, U1.16, U2.1, U2.16, U3.20, U4.14
